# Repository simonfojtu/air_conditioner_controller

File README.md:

# Air conditioner controller

Controller for an air conditioner unit

manufacturer: ACOND
models: AS-12UR4SYDDA, AS-09UR4SYDDA

## IR receiver and display module

connected to main unit via 5 wires:
- YK (orange)
- KEY (yellow)
- SDA1 (greenish)
- +5V (blue)
- GND (purple)

JST-SM 2.5mm connector, male connector view from the key side, cables going up: leftmost = gnd

- YK and KEY seems to be high (5V) all the time, except for some noise spikes
- SDA1 carries a signal, repeating slightly faster than 1Hz, presumably bidirectional, since the front unit needs to know the current temperature.single pulse is 5/6ms. i.e. 1.2kHz

=================
## ESP 8266 troubleshooting

http://www.esp8266.com/viewtopic.php?p=24592

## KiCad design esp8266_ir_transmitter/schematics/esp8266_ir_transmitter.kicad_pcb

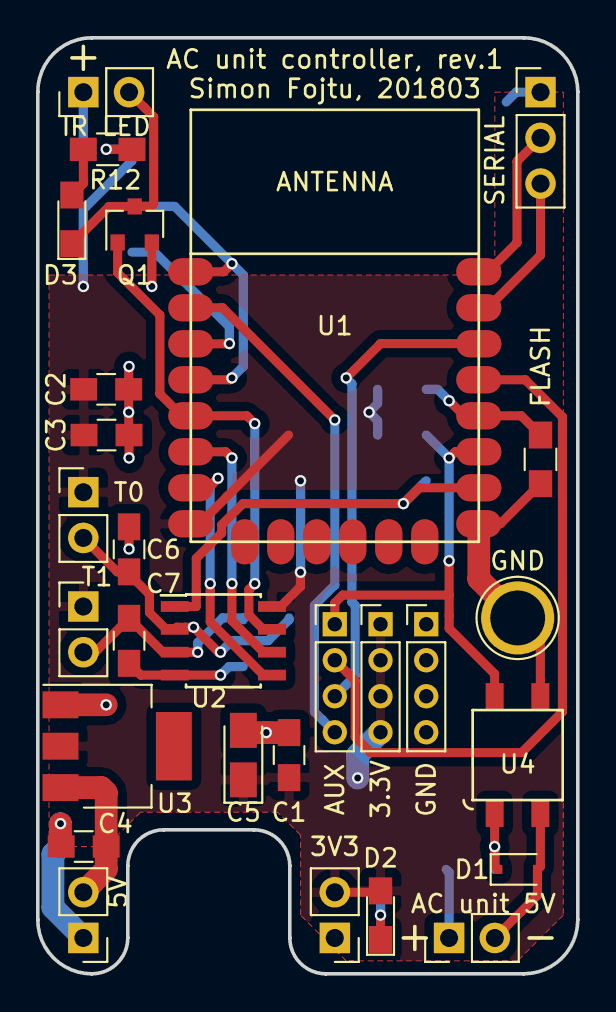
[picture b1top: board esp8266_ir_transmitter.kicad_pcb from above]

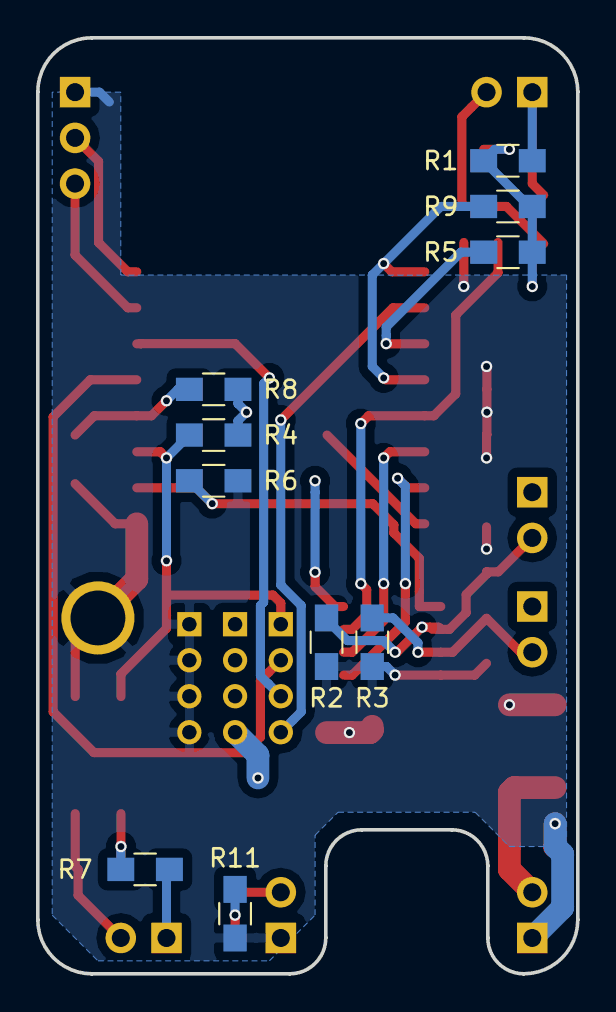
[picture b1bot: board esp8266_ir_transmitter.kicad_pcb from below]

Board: 2 copper layers, 30.0 x 52.0 mm, 38 parts (10 on the bottom side), 25 nets.

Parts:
C1, C3, C6, C7: 100n; C_0805_HandSoldering
C2: 10n; C_0805_HandSoldering
C4: 1uF, cer.; C_0805_HandSoldering
C5: 10uF, tant.; CP_Tantalum_Case-A_EIA-3216-18_Reflow
D1: BAS16J.115; D_SOD-323F
D2: power; LED_0805_HandSoldering
D3: LED; LED_0805_HandSoldering
P1: SERIAL; Pin_Header_Straight_1x03_Pitch2.54mm
P2: IR LED; Pin_Header_Straight_1x02_Pitch2.54mm
P3: 5V; Pin_Header_Straight_1x02_Pitch2.54mm
P4: 3V3; Pin_Header_Straight_1x02_Pitch2.54mm
P7: T0; Pin_Header_Straight_1x02_Pitch2.54mm
P10: T1; Pin_Header_Straight_1x02_Pitch2.54mm
P11: GND; 1pin
P12: AUX; Pin_Header_Straight_1x04_Pitch2.00mm
P13: GND; Pin_Header_Straight_1x04_Pitch2.00mm
P14: 3.3V; Pin_Header_Straight_1x04_Pitch2.00mm
P15: AC unit 5V; Pin_Header_Straight_1x02_Pitch2.54mm
Q1: 2N7002; SOT-23
R1, R6, R11, R12: 1k; R_0805_HandSoldering
R2, R3, R4, R7: R; R_0805_HandSoldering
R5, R8: 4k7; R_0805_HandSoldering
R9: 10k; R_0805_HandSoldering
R10: FLASH; R_0805_HandSoldering
U1: ESP-12-Q; esp8266-12-q
U2: MCP3002; SOIC-8_3.9x4.9mm_Pitch1.27mm
U3: LD1117S33TR; SOT-223
U4: LTV-356T

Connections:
+3V3: C1.1, C2.1, C3.1, C5.1, D2.2, P4.2, P7.1, P10.1, P14.1, P14.2, P14.3, P14.4, R1.1, R4.1, R5.1, R8.1, R9.2, R12.1, U1.8, U2.8, U3.2
+5V: C4.1, P3.2, U3.3
/ADC: P12.4, U1.2
/EN: R5.2, U1.3
/GPIO0: R8.2, R10.1, U1.18
/GPIO2: P12.1, R4.2, U1.17, U4.4
/GPIO4: P12.2, U1.19
/GPIO5: P12.3, U1.20
/GPIO12: U1.6, U2.6
/GPIO13: U1.7, U2.5
/GPIO14: Q1.1, U1.5, U2.7
/GPIO15: R6.2, U1.16, U2.1
/GPIO16: R9.1, U1.1, U1.4
/RX: P1.3, U1.21
/TX: P1.2, U1.22
GND: C1.2, C2.2, C3.2, C4.2, C5.2, C6.2, C7.2, P1.1, P3.1, P4.1, P11.1, P13.1, P13.2, P13.3, P13.4, Q1.2, R2.2, R3.2, R6.1, R10.2, R11.2, U1.15, U2.4, U3.1, U4.3
unnamed: C6.1, P7.2, R2.1, U2.2
unnamed: C7.1, P10.2, R3.1, U2.3
unnamed: D1.1, R7.2, U4.1
unnamed: D1.2, P15.2, U4.2
unnamed: D2.1, R11.1
unnamed: D3.1, P2.2, Q1.3
unnamed: D3.2, R12.2
unnamed: P2.1, R1.2
unnamed: P15.1, R7.1

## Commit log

2018-03-18 Arduino sketch to record IR commands from the original IR controller.
2018-03-18 Python script to parse recorded IR commands
2018-03-18 Recorded data
2018-03-18 PCB rev1
2018-03-19 PCB revision 1
2018-04-13 external repo for mqtt implementation
2018-04-22 Add submodule MetalPhreak/ESP8266_SPI_Driver
2018-04-23 Add Air conditioner unit and IR transmit related code
2018-04-23 Add include/*
2018-04-23 Add initenv template
2018-04-24 updated initenv
2018-04-25 Renamed initenv to initenv.template
2018-04-25 Add libesphttpd as submodule
2018-04-25 Httpd server based on esphttpd; added AC control page
2018-04-25 Fixed on/off toggle always true
2018-04-26 Removed wrong paths from Makefile
2018-04-26 Removed submodule mqtt
2018-04-26 Added submodule mqtt
2018-04-26 Updated makefiles
2018-04-26 add mqtt local config
2018-04-26 mqtt
2018-04-26 mqtt still alive cleanup
2018-04-28 Main cleanup
2018-04-28 moving spi library
2018-04-29 Reading temperature via NTC and MCP3002 over SPI
2018-04-29 Reduced uart messages
2018-05-02 OTA updates
2018-05-02 Note about front panel to guts cable connector pinout
2018-05-03 Parsing mqtt commands and sending IR commands to the AC unit
2018-05-11 Fixed sending temperatures update without leading space
2018-05-11 Temperature read on AC init
2018-05-16 Code cleanup
2018-05-16 Change of AC API
2018-05-18 Fan and mode are adjustable via mqtt
2018-05-18 Updated initenv template for OTA updatE
2018-05-20 Openhab2 actually listens to state (setpoint, fan, mode, ..); reduced update rate to every 20s
2018-05-21 Updated comment about why SPI does not work after IR command is sent
2018-05-21 Fixups - compilation warnings
2018-05-22 Updated README with info on SDA1 signal
2018-05-22 Fixups of esp8266 ir transmitter schematics for next revision
